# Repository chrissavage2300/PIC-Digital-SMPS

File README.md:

# PIC-Digital-SMPS
This is a digital SMPS that I designed with current sensing capablitlies. It is powered from a PIC18F13K22, but any PIC will work that has the same pinout. The PIC runs at 64Mhz to output a 250Khz signal used in half bridge mode. 
Input: 15V Max
Output: Not tested, but 0 to 15V
Iout(max):Not tested, 2A

Has spare outputs for Red,Green,and Blue LEDs. 
UART/I2C Connectors for board to board communications
PIC16F series with 16Bit PWM should work as well. 

Note: Current schematic (9/4/2018) has PGC and PGD reversed on the programming side. Just reverse the connections with a wire and it will work.

0

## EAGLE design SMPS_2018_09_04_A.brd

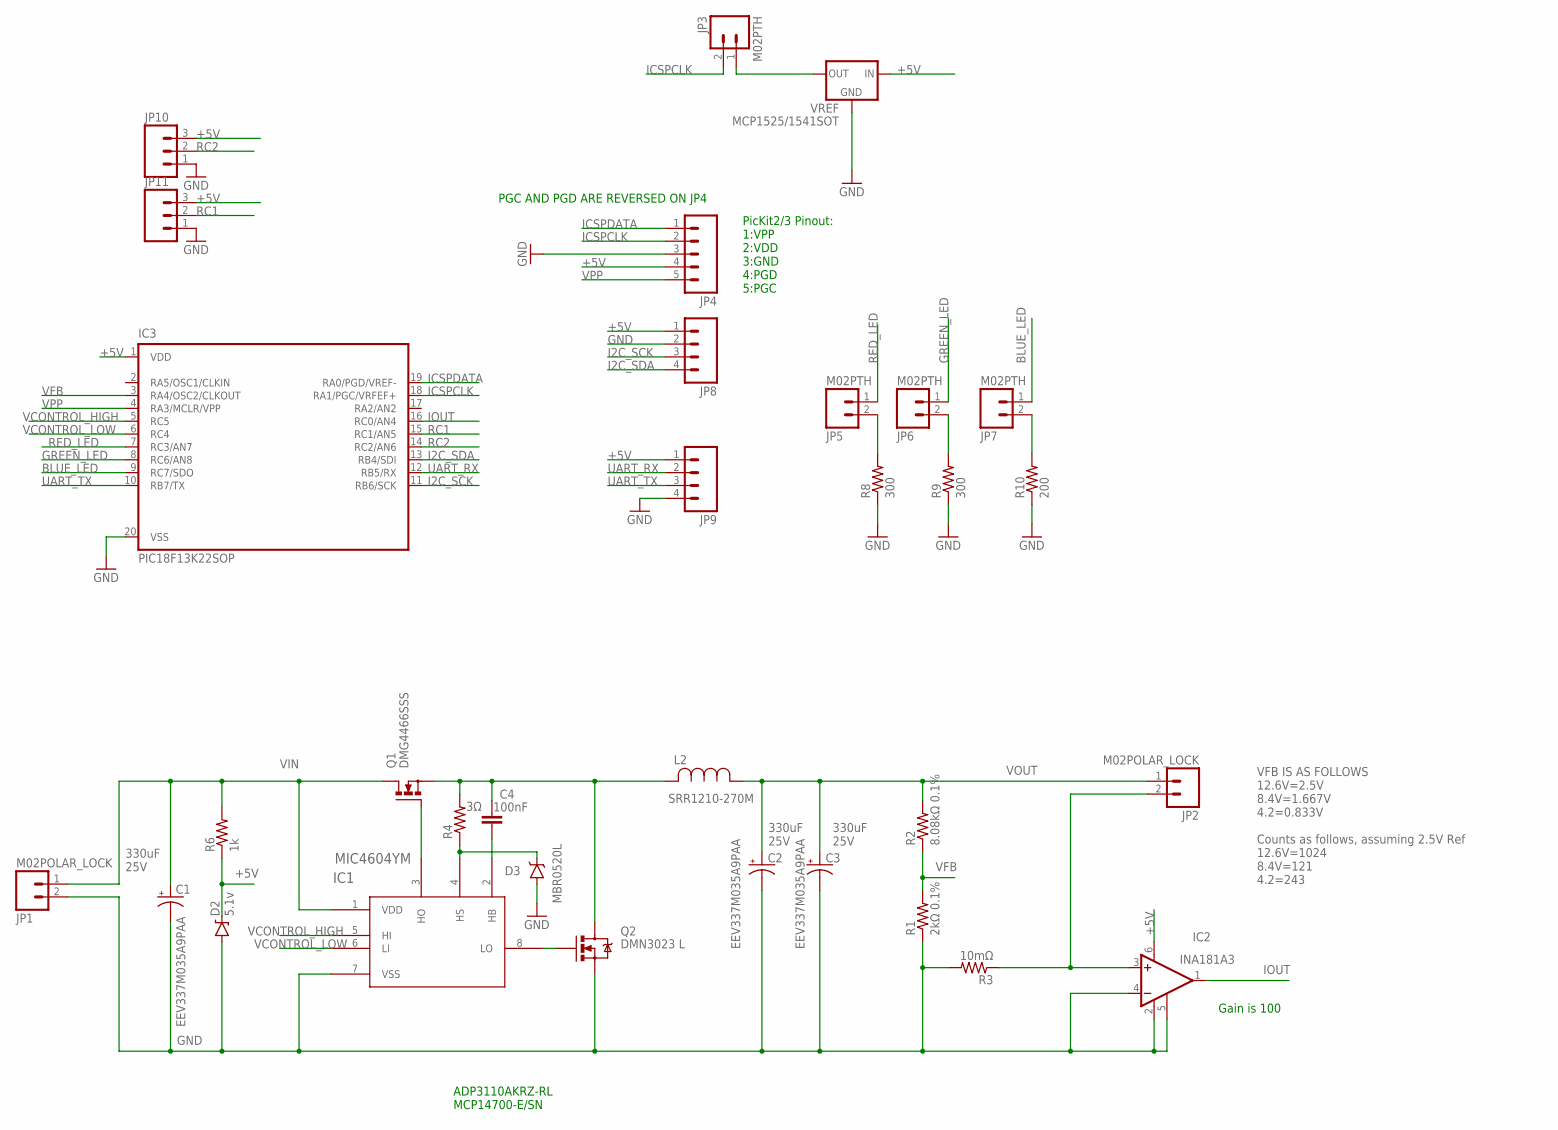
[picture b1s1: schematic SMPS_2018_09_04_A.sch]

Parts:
C1, C2, C3: EEV337M035A9PAA; 140CLH-1010
C4: 100nF; 1206
D2: 5.1v; SMB-DIODE
D3: MBR0520L; SMA-DIODE
IC1: MIC4604YM; SOIC-8_M
IC2: INA181A3; SOT23-6
IC3: PIC18F13K22SOP; SOP20W
JP1, JP2: M02POLAR_LOCK; MOLEX-1X2_LOCK
JP3, JP5, JP6, JP7: M02PTH; 1X02
JP4: M05PTH_LONGPADS; 1X05_LONGPADS
JP8, JP9: M04LOCK; 1X04_LOCK
JP10, JP11: M03LOCK; 1X03_LOCK
L2: SRR1210-270M; IND_BOURNS_SRR1210
Q1: DMG4466SSS; SO-08
Q2: DMN3023 L; SOT23-3
R1: 2kΩ 0.1%; 1206
R2: 8.08kΩ 0.1%; 1206
R3: 10mΩ; 1206
R4: 3Ω; 1206
R6: 1k; 1206
R8, R9: 300; 1206
R10: 200; 1206
VREF: MCP1525/1541SOT; SOT23-3

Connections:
+5V: D2.C, IC2.6 (V+), IC3.1 (VDD), JP4.4, JP8.1, JP9.1, JP10.3, JP11.3, R6.1, VREF.1 (IN)
BLUE_LED: IC3.9 (RC7/SDO), JP7.1
BORKED: IC2.3 (+IN), JP2.2, R3.1
GND: C1.-, C2.-, C3.-, D2.A, D3.A, IC1.7 (VSS), IC2.2 (GND), IC2.4 (-IN), IC2.5 (REF), IC3.20 (VSS), JP1.2, JP4.3, JP8.2, JP9.4, JP10.1, JP11.1, Q2.2 (S), R1.1, R3.2, R8.1, R9.1, R10.1, VREF.3 (GND)
GREEN_LED: IC3.8 (RC6/AN8), JP6.1
HIGHDRIVE: IC1.3 (HO), Q1.4 (G)
I2C_SCK: IC3.11 (RB6/SCK), JP8.3
I2C_SDA: IC3.13 (RB4/SDI), JP8.4
ICSPCLK: IC3.18 (RA1/PGC/VRFEF+), JP3.2, JP4.2
ICSPDATA: IC3.19 (RA0/PGD/VREF-), JP4.1
IOUT: IC2.1 (OUT), IC3.16 (RC0/AN4)
unnamed: C4.2, L2.2, Q1.1 (S), Q1.2 (S), Q1.3 (S), Q2.3 (D), R4.2
unnamed: JP5.2, R8.2
unnamed: C4.1, IC1.2 (HB)
unnamed: IC1.8 (LO), Q2.1 (G)
unnamed: JP6.2, R9.2
unnamed: JP7.2, R10.2
unnamed: D3.C, IC1.4 (HS), R4.1
RC1: IC3.15 (RC1/AN5), JP11.2
RC2: IC3.14 (RC2/AN6), JP10.2
RED_LED: IC3.7 (RC3/AN7), JP5.1
UART_RX: IC3.12 (RB5/RX), JP9.2
UART_TX: IC3.10 (RB7/TX), JP9.3
VCONTROL_HIGH: IC1.5 (HI), IC3.5 (RC5)
VCONTROL_LOW: IC1.6 (LI), IC3.6 (RC4)
VFB: IC3.3 (RA4/OSC2/CLKOUT), R1.2, R2.1
VIN: C1.+, IC1.1 (VDD), JP1.1, Q1.5 (D), Q1.6 (D), Q1.7 (D), Q1.8 (D), R6.2
VOUT: C2.+, C3.+, JP2.1, L2.1, R2.2
VPP: IC3.4 (RA3/MCLR/VPP), JP4.5
VREF+: JP3.1, VREF.2 (OUT)

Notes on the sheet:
ADP3110AKRZ-RL MCP14700-E/SN
Gain is 100
330uF 25V
VFB IS AS FOLLOWS 12.6V=2.5V 8.4V=1.667V 4.2=0.833V Counts as follows, assuming 2.5V Ref 12.6V=1024 8.4V=121 4.2=243
PicKit2/3 Pinout: 1:VPP 2:VDD 3:GND 4:PGD 5:PGC
PGC AND PGD ARE REVERSED ON JP4

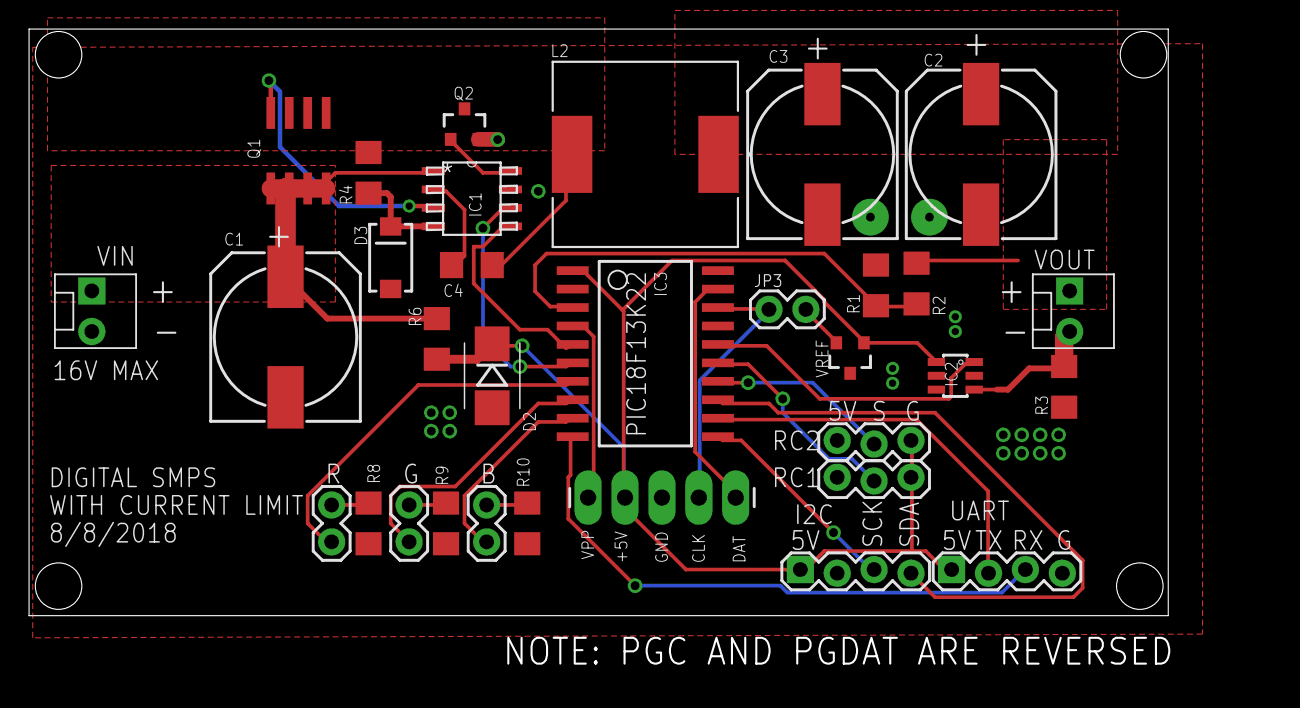
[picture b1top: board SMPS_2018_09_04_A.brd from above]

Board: 2 copper layers, 85.5 x 44.7 mm, 32 parts (0 on the bottom side), 30 nets.

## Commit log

2018-10-18 Create BetaCode_2018_10_18

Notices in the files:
parts and their libraries:
SparkFun-DiscreteSemi: Licensing: Creative Commons ShareAlike 4.0 International - https://creativecommons.org/licenses/by-sa/4.0
